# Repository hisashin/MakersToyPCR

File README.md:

## [We're fighting with COVID-19 by upgrading NinjaPCR into affordable Real-Time PCR.](https://github.com/hisashin/NinjaPCR/wiki/NinjaPCR's-fight-with-COVID-19)

NinjaPCR is Opensource(GPLv3) DNA Amplifier,Thermocycler Implementation for [Polymerase Chain Reaction](http://en.wikipedia.org/wiki/Polymerase_chain_reaction) developed by [Shingo Hisakawa](https://www.facebook.com/hisakawa) and [Mariko Hisakawa](https://www.facebook.com/maripo).<br />

Check [support site](https://ninjapcr.tori.st) for more infomations including how to [make](https://ninjapcr.tori.st/maker/) it. BOM is [here](https://docs.google.com/spreadsheets/d/1QYWESJrQ2N63OPvq1pnQvB-iVQkymN-hYeTYLx7xuOw/edit?usp=sharing).

Forked from [OpenPCR](https://github.com/jperfetto/OpenPCR).

Major changes from OpenPCR:<br />
01. Smaller and [easier to build](https://ninjapcr.tori.st/assy/index.html)<br />
02. Change platform from Adobe AIR to WiFi. Almost all PC and smartphones are supported<br />
03. LCD removed. Everything on Browser<br />
04. Keep precision from low to high temperature<br />
05. Auto update for new features (ex. IFTTT support scheduled)<br />
06. It's still [on sale](https://shop.tori.st) (OpenPCR is [discontinued](https://www.chaibio.com/openpcr))

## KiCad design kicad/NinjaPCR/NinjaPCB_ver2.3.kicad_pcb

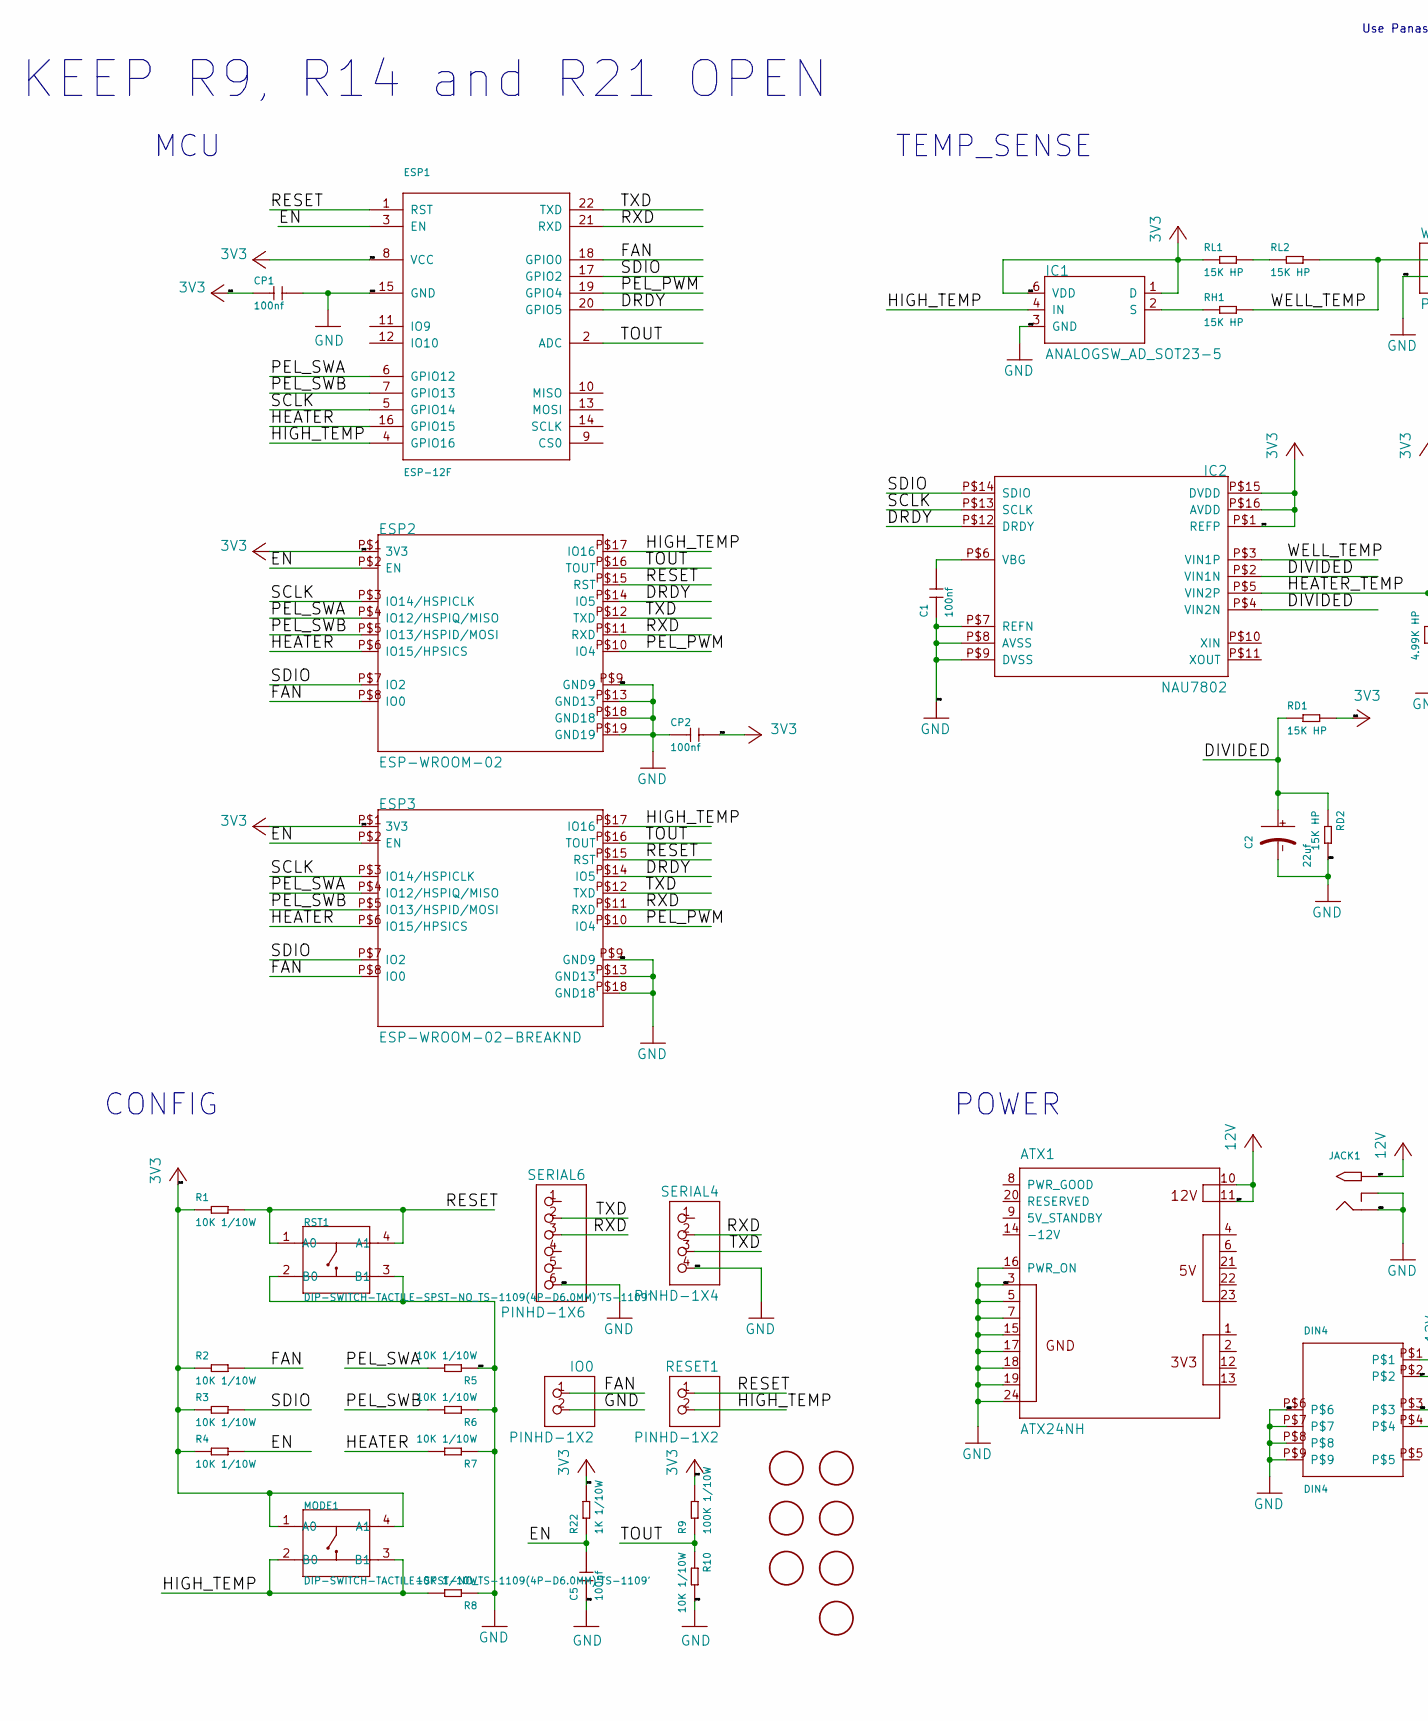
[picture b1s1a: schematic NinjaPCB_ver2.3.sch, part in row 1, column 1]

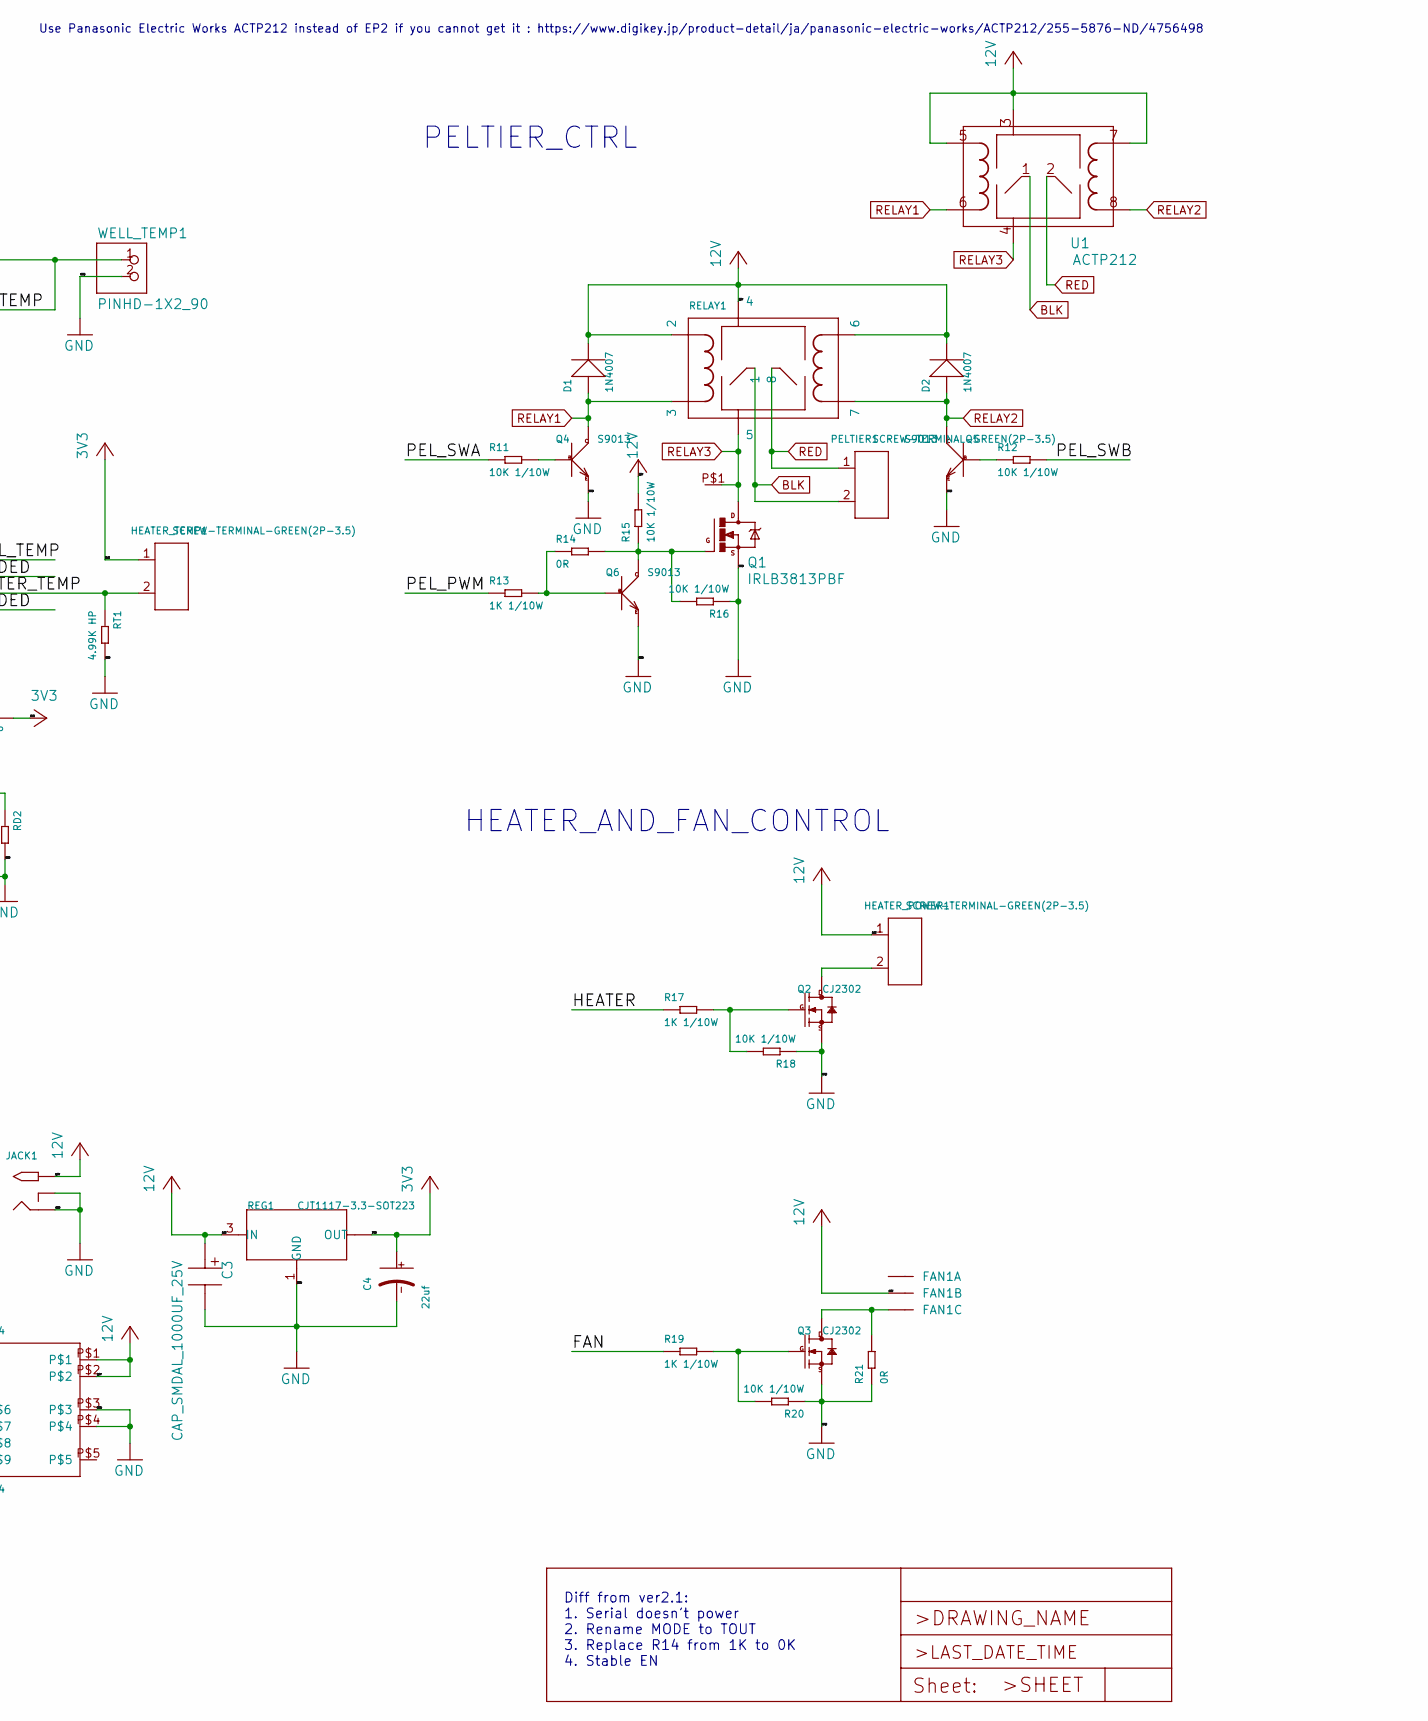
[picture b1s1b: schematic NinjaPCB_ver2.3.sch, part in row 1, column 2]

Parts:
ATX1: ATX24NH; ATX24
C1, C5: 100nf; C0603
C2, C4: 22uf; AVX-B
C3: CAP_SMDAL_1000UF_25V; CAP_SMD_AL_D125
CP1, CP2: 100nf; C0603
D1, D2: 1N4007; DO-214AC
DIN4: DIN4
ESP1: ESP-12F
ESP2: ESP-WROOM-02
ESP3: ESP-WROOM-02-BREAKND; ESP-WROOM-02-BREAK-NODETAIL
FAN1: 22-23-2031
HEATER_POWER1: SCREW-TERMINAL-GREEN(2P-3.5); H2-3.5-7.0X7.0MM
HEATER_TEMP1: SCREW-TERMINAL-GREEN(2P-3.5); H2-3.5-7.0X7.0MM
HEATSINK1: HEAT111PB015; HEAT11PB015
IC1: ANALOGSW_AD_SOT23-5; SOT23-5
IC2: NAU7802; SOP-16
IO0: PINHD-1X2; 1X02
JACK1: 2.1MMJACKTHM-NOOUT; PJ-102A-NOOUT
MODE1: DIP-SWITCH-TACTILE-SPST-NO_TS-1109(4P-D6.0MM)'TS-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; SW4-6.0X6.0X5.0MM
PELTIER1: SCREW-TERMINAL-GREEN(2P-3.5); H2-3.5-7.0X7.0MM
Q1: IRLB3813PBF; TO220BV
Q2, Q3: CJ2302; SOT-23
Q4, Q5, Q6: S9013; SOT-23
R1, R2, R3, R4, R5, R6, R7, R8, R10, R11, R12, R15, R16, R18, R20: 10K 1/10W; R0603
R9: 100K 1/10W; R0603
R13, R17, R19, R22: 1K 1/10W; R0603
R14, R21: 0R; R0603
RD1, RD2: 15K HP; R0603
REG1: CJT1117-3.3-SOT223; SOT-223
RELAY1: NEC-RELAY2EP2; NEC-EP2
RESET1: PINHD-1X2; 1X02
RH1: 15K HP; R0603
RL1, RL2: 15K HP; R0603
RST1: DIP-SWITCH-TACTILE-SPST-NO_TS-1109(4P-D6.0MM)'TS-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; SW4-6.0X6.0X5.0MM
RT1: 4.99K HP; R0603
SERIAL4: PINHD-1X4; 1X04
SERIAL6: PINHD-1X6; 1X06
U1: ACTP212
U$3, U$4, U$5, U$7, U$8, U$9, U$10: FIDUCIAL; FIDUCIAL_1MM
WELL_TEMP1: PINHD-1X2_90; 1X02_90

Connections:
/DIVIDED: C2.+, IC2.P$2 (VIN1N), IC2.P$4 (VIN2N), RD1.1, RD2.1
/DRDY: ESP1.20 (GPIO5), ESP2.P$14 (IO5), ESP3.P$14 (IO5), IC2.P$12 (DRDY)
/EN: C5.2, ESP1.3 (EN), ESP2.P$2 (EN), ESP3.P$2 (EN), R4.2, R22.1
/FAN: ESP1.18 (GPIO0), ESP2.P$8 (IO0), ESP3.P$8 (IO0), IO0.1, R2.2, R19.1
/HEATER: ESP1.16 (GPIO15), ESP2.P$6 (IO15/HPSICS), ESP3.P$6 (IO15/HPSICS), R7.2, R17.1
/HEATER_TEMP: HEATER_TEMP1.2, IC2.P$5 (VIN2P), RT1.1
/HIGH_TEMP: ESP1.4 (GPIO16), ESP2.P$17 (IO16), ESP3.P$17 (IO16), IC1.4 (IN), MODE1.2 (B0), MODE1.3 (B1), R8.2, RESET1.2
/PEL_PWM: ESP1.19 (GPIO4), ESP2.P$10 (IO4), ESP3.P$10 (IO4), R13.1
/PEL_SWA: ESP1.6 (GPIO12), ESP2.P$4 (IO12/HSPIQ/MISO), ESP3.P$4 (IO12/HSPIQ/MISO), R5.2, R11.1
/PEL_SWB: ESP1.7 (GPIO13), ESP2.P$5 (IO13/HSPID/MOSI), ESP3.P$5 (IO13/HSPID/MOSI), R6.2, R12.2
/RESET: ESP1.1 (RST), ESP2.P$15 (RST), ESP3.P$15 (RST), R1.2, RESET1.1, RST1.1 (A0), RST1.4 (A1)
/RXD: ESP1.21 (RXD), ESP2.P$11 (RXD), ESP3.P$11 (RXD), SERIAL4.2, SERIAL6.3
/SCLK: ESP1.5 (GPIO14), ESP2.P$3 (IO14/HSPICLK), ESP3.P$3 (IO14/HSPICLK), IC2.P$13 (SCLK)
/SDIO: ESP1.17 (GPIO2), ESP2.P$7 (IO2), ESP3.P$7 (IO2), IC2.P$14 (SDIO), R3.2
/TOUT: ESP1.2 (ADC), ESP2.P$16 (TOUT), ESP3.P$16 (TOUT), R9.1, R10.1
/TXD: ESP1.22 (TXD), ESP2.P$12 (TXD), ESP3.P$12 (TXD), SERIAL4.3, SERIAL6.2
/WELL_TEMP: IC2.P$3 (VIN1P), RH1.2, RL2.2, WELL_TEMP1.1
BLK: PELTIER1.2, RELAY1.P$1 (1), U1.1
GND: ATX1.3 (GND3), ATX1.5 (GND5), ATX1.7 (GND7), ATX1.15 (GND15), ATX1.16 (PWR_ON), ATX1.17 (GND17), ATX1.18 (GND18), ATX1.19 (GND19), ATX1.24 (GND24), C1.1, C2.-, C3.P$M, C4.-, C5.1, CP1.2, CP2.1, DIN4.P$3, DIN4.P$4, DIN4.P$6, DIN4.P$7, DIN4.P$8, DIN4.P$9, ESP1.15 (GND), ESP2.P$9 (GND9), ESP2.P$13 (GND13), ESP2.P$18 (GND18), ESP2.P$19 (GND19), ESP3.P$9 (GND9), ESP3.P$13 (GND13), ESP3.P$18 (GND18), IC1.3 (GND), IC2.P$7 (REFN), IC2.P$8 (AVSS), IC2.P$9 (DVSS), IO0.2, JACK1.RING, JACK1.RING_SW, Q1.S, Q2.2 (S), Q3.2 (S), Q4.2 (E), Q5.2 (E), Q6.2 (E), R5.1, R6.1, R7.1, R8.1, R10.2, R16.1, R18.1, R20.1, R21.1, RD2.2, REG1.1 (GND), RST1.2 (B0), RST1.3 (B1), RT1.2, SERIAL4.4, SERIAL6.6, WELL_TEMP1.2
unnamed: C1.2, IC2.P$6 (VBG)
unnamed: FAN1.3, Q3.3 (D), R21.2
unnamed: HEATER_POWER1.2, Q2.3 (D)
unnamed: IC1.2 (S), RH1.1
unnamed: Q1.G, Q6.3 (C), R14.2, R15.1, R16.2
unnamed: Q2.1 (G), R17.2, R18.2
unnamed: Q3.1 (G), R19.2, R20.2
unnamed: Q4.1 (B), R11.2
unnamed: Q5.1 (B), R12.1
unnamed: Q6.1 (B), R13.2, R14.1
unnamed: RL1.2, RL2.1
RED: PELTIER1.1, RELAY1.P$8 (8), U1.2
RELAY1: D1.1 (+), Q4.3 (C), RELAY1.P$3 (3), U1.6
RELAY2: D2.1 (+), Q5.3 (C), RELAY1.P$7 (7), U1.8
RELAY3: HEATSINK1.P$1, Q1.D, RELAY1.P$5 (5), U1.4

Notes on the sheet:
TEMP_SENSE
HEATER_AND_FAN_CONTROL
PELTIER_CTRL
MCU
POWER
Diff from ver2.1: 1. Serial doesn't power 2. Rename MODE to TOUT 3. Replace R14 from 1K to 0K 4. Stable EN
CONFIG
KEEP R9, R14 and R21 OPEN
Use Panasonic Electric Works ACTP212 instead of EP2 if you cannot get it : https://www.digikey.jp/product-detail/ja/panasonic-electric-works/ACTP212/255-5876-ND/4756498

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
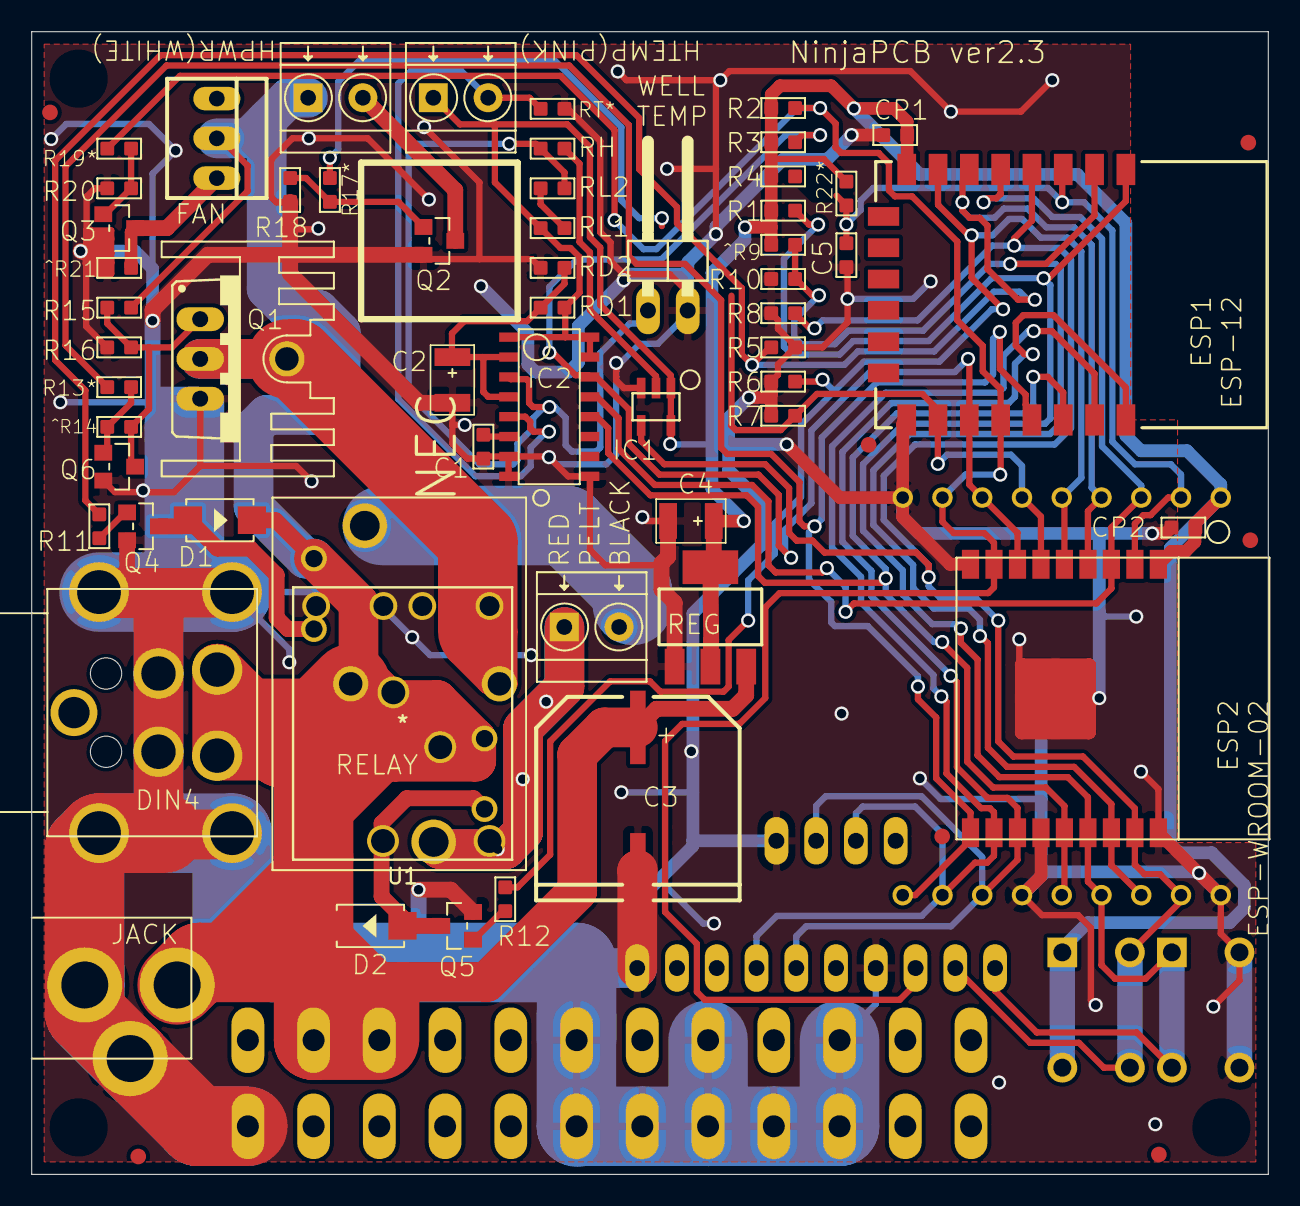
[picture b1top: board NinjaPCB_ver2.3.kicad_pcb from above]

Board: 2 copper layers, 79.0 x 73.0 mm, 73 parts (0 on the bottom side), 35 nets.

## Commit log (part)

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2014-08-18 Detailing REAME
2014-12-01 Fix but in port scanning code
2014-12-01 Add syncFileSystem permission to manifest file (chrome)
2014-12-01 Modify .gitignore by adding *~ (emacs tmp files)
2014-12-01 Add test buttons & skeleton of dev code
2014-12-02 Check quota of sync filesystem
2015-03-05 Correct the firmware version
    * Correct the firmware version in resource files to stop showing wrong "update" dialog
    * Add version
    * Fix a typo in the build shell
2015-03-05 Add nde debug feature
    * Replace console.log, info, warn, error with custom functions
    * Add debug textarea to the top panel
2015-03-05 Add version (1.1.4 -> 1.1.5)
2015-03-05 Fix build shell script
2015-08-04 add pcbs
2015-08-04 add readme
2015-08-04 refresh all data to latest
2015-08-05 write BOM url clearly
2015-10-19 remove unused pcbs
2015-10-20 rename for easy understanding
2015-10-22 link to wiki
2015-12-18 export lasercut data as ai and pdf
2016-01-06 add values of reg&cap
2016-02-05 update sheet->grease
2016-02-07 add tapping instructions
2016-03-06 add handle
2016-11-12 Use same values in sch and brd
2016-11-12 remove unused files
2016-11-20 well block is updated to hold tubes perfectly
2016-11-20 CAM of well added
2016-11-26 update toolpath Tube2
2017-06-19 Show alert section when opened as a web page
2017-06-28 Fix compilation error with ESP8266
2017-07-01 Add WiFi demo code
    * Fix compilation problem
    * Add WiFi edition specific config
2017-07-03 Use abstract class "Communicator"
2017-07-04 Implement JSONP communication system
2017-07-04 Test WiFi + JSONP
2017-07-05 Implement WiFi + Browser app communication
2017-07-05 Implement storage functionalities for WiFi edition
2017-07-05 Use TOUT pin of ESP8288
2017-07-05 Use on/off control to control lid heater
2017-07-06 Implement firmware verison checker
2017-09-02 preparing NinjaPCB ver2 using Seeed OPL
2017-09-02 fixing things
2017-09-28 add evaluation board for NinjaPCB ver2
2017-10-04 Define analog switch pin for 2-range temperature measurement
2017-10-04 Switch WiFi mode with HIGH_TEMP pin
2017-10-04 Implement AP mode logic
2017-10-04 Save & load wifi connection information
2017-10-04 Add link to PCR configuration guide
2017-10-05 Refactor / Implement IP address notification system
2017-10-05 Compare IP address
2017-10-06 completed ver2-170831
2017-10-09 ordered pcb
2017-10-12 Implement WiFi init functionalities
2017-12-01 remove ver2 temporary. it will be back after evaluation.
2017-12-12 Support two types of ADC (SPI MCP3554 & NAU7803)
2017-12-27 Fix AP mode bug
2018-01-02 Implement OTA sequence
2018-01-11 pushed again to share with mariko. do not manufacture it yet
2018-01-16 add memos
2018-01-17 pulldown HEATER to write
2018-01-17 VNH5019 doesnot have same pinout as VNH3SP30
2018-01-23 Implement I2C ADC
2018-01-29 use relay instead of driver
2018-01-29 remove images of first version
2018-01-29 add ESP-12F-breakout compatible with ESP-WROOM-02-breakout
2018-01-29 use breakout board
2018-02-08 latest updates
2018-02-27 Designing 2nd ver2 board. DO NOT make first NinjaPCB_ver2-170831.brd
2018-03-03 finished
2018-03-03 remove errored one
2018-03-03 to be ordered
2018-03-04 npn to pnp. added pullups and pulldowns
2018-03-04 added hole for gromet #digikey 36-733-ND
2018-03-08 version control
2018-03-08 changed R14 into RT. no reason for T
2018-03-08 add low ESR cap to standard voltage for NAU7802
2018-03-09 Support Relay (for replacement of motor driver IC)
2018-03-13 replace 2d data to ver2 dxf
2018-03-15 add MODE jumper to use same source for 4x4 and 2x2
2018-03-15 add MooMoo ones
2018-03-16 split into 2 subprojects : 4x4 NinNin and 2x2 MooMoo
2018-03-17 use easier parts. add notes to design
2018-03-18 abstract layout image of 2x2MooMoo
2018-03-19 Implement mDNS functionalities
2018-03-22 change values of MOSFET G-S reg
2018-03-26 start wiring NinNin ver2.0
2018-03-30 wired
2018-03-30 dru clear
2018-03-30 minor tunes
2018-03-31 ready to order
2018-04-01 panelized NinNin
2018-04-01 prepare for order
2018-04-04 ordered
2018-04-05 Fix NAU7802 library
2018-04-05 Rename NAU7803->NAU7802
2018-04-08 shrink panel
2018-04-11 Implement local test
2018-04-11 set distance more equal 10mil for 2oz at Seeed
2018-04-12 Fix bugs (PID related logic, relay control etc.)
2018-04-17 Amplification test
2018-04-18 set default 4x4
2018-04-19 remove wrong schematics
2018-04-19 reset
2018-04-26 Implement WiFi communication / bug fix
2018-04-26 Update lasercut data
2018-04-26 add svg
2018-04-26 update 2d/3d info
2018-04-26 add eps
2018-04-27 Enhance network functionalities
2018-05-01 Simplify WiFi related code
2018-05-01 CDN test
2018-05-01 add image
2018-05-02 Organize constants related to thermistors and their counter resistors
2018-05-03 Amplification demo
2018-05-06 Implement sample temp estimation logic
2018-05-10 Separate OTA logic as Update.ino# Please enter the commit message for your changes. Lines starting
2018-05-10 Remove unused file
2018-05-10 Add binary
2018-05-10 Enhance OTA functionalities
2018-05-14 Fixed board config according to 2.0 schematics
2018-05-14 Restart device after saving WiFi config
2018-05-14 update dxf
2018-05-17 Implemented SSL update
2018-05-17 Add Update logic files
2018-05-17 Prepare for thermistor ADC improvement
2018-05-17 Implement basic switching logic
2018-05-17 Implement well<=>lid ADC switching logic
2018-05-21 ver2.1 finished
2018-05-23 minor update of silk
2018-05-25 minor update for layout
2018-05-29 Imprement ADC error handling
2018-05-30 Implemented hardware check for safety
2018-06-03 add manufacture
2018-06-03 update cdr
2018-06-03 share t5.0 model
2018-06-03 ignore autogen backup files of CorelDRAW
2018-06-12 Added error handling and WiFi reconnection feature
2018-06-12 Send error code
2018-06-14 .gitignore
2018-06-18 update laser
2018-06-19 cdr updated
2018-06-25 Implement hardware error detection
2018-06-27 PID tuning
2018-06-27 Implemented top page of server mode
2018-06-29 Support board 2.1
2018-06-29 Toggle debug message
2018-06-30 NinjaPCB ver2.2
2018-07-03 Stabilize ADC (especially in first boot)
2018-07-03 Display previous status/error of WiFi config
2018-07-03 Switch peltier pin in hardware init sequence
2018-07-06 Release 1.0.1
2018-07-06 Add rampElapsedTimeMsec to CyclerStatus struct
2018-07-06 Use ramping time when checking peltier device's health
2018-07-08 Use max and min temperature in hardware check
2018-07-08 Fix bug in peltier checker logic
2018-07-19 update front panel
2018-07-23 sync
2018-07-23 add NinjaPCR 2.2
2018-07-23 fixed NinjaPCB ver 2.2
2018-07-24 updated 2.2
2018-07-24 fixed 2.2
2018-07-24 remove zip from eagle
2018-08-09 add zip
2018-08-20 add models
2018-08-21 ChromeApp is out of support
2018-08-27 update words
2018-08-27 Add version
2018-08-27 remove chrome
2018-08-27 remove ver1.0
2018-10-17 Release firmware 1.0.12
    * Use ESP8266 2.4.2
    * Insert delay before resetting
2018-11-08 Pause heating units while processing HTTP requests
    * Change order of network and thermal cycler functions
    * Add "PauseHeatingUnits" function
    * Rename some members of Thermocycler class
2018-11-08 Remove unused functions
2018-11-08 Calculate and set power output ratio
2018-11-08 Use power outupt ratio when setting lid & peltier PWM values
    For safety, heating units are stopped while the HTTP server is responding.
    To compensate the off time, PWM values are amplified according to network
    response time.
2018-11-09 Fix bug (SetPowerOutputRatio was called in error handling block by mistake)
2018-11-09 Fix peltier driver bug
2018-11-10 Send signed value of Peltier drive instead of absolute value #11
2018-11-11 Consider balance of Peltier's internal heat and cooling efficiency
2018-11-11 Add version (1.0.13)
2018-11-13 Show MAC address on WiFi config view
2018-12-07 Add stubs of Pause/Resume/NextStep/NextCycle
2018-12-07 Implement pause/resume functionalities
    * Altered logic of calculating ramp & hold elapsed time
    * Parse commands from UI
    * Send response
2018-12-11 Send total cycles count and current cycle index
2019-01-10 Control next step/cycle flags
2019-01-10 Advance to next step by command
2019-01-10 Check if the step is "final" or not when receiving "next step" command
2019-01-24 Implement step/cycle skip
    * Accept next step / next cycle commands
    * Add version (1.1)
2019-01-27 Reconsider the hard-coded firmware server
    It would be more convenient if "firmwareHost" is set to the one that the machine is actually connected to, not the explicit host.
2019-03-19 AP mode
2019-03-20 Completed AP mode support
2019-04-03 add link to BOM
2019-04-15 Fix wrong error code / Add comments
2020-03-17 correct link
2020-04-13 remove unused data
2020-10-29 Add version / Fix "Error9" on very low temperature
2021-01-04 Fix threshold of hardware error detection logic
2021-03-31 Updated alert threshold of heating/cooling rate
2021-04-16 found another relay to H bridge but not wired
2021-04-16 add link
2021-05-10 add front panel to print for maker model

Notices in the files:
parts and their libraries:
Copyright 2016 Accelerated Designs. All rights reserved.
